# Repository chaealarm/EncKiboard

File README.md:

# EncKiboard V3
RP2040, MX keys with LED, 1 Encoder   

Designed in EasyEDA

## See also
Arduino Board Library(Generic RP2040) : https://github.com/earlephilhower/arduino-pico

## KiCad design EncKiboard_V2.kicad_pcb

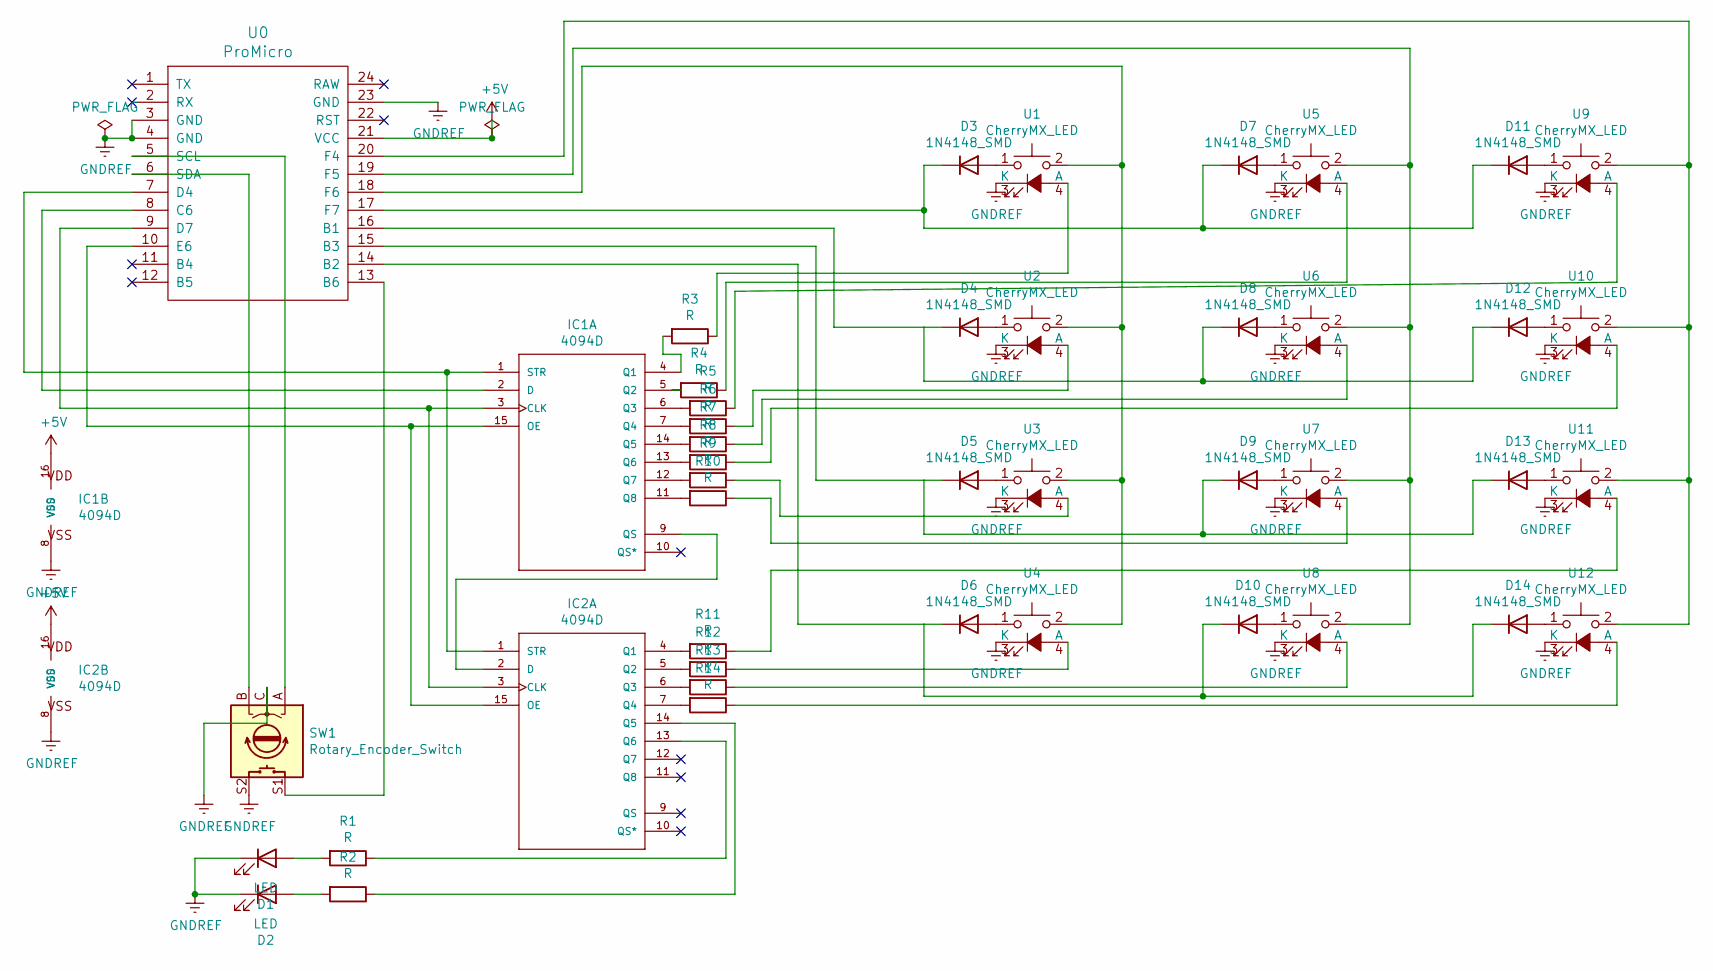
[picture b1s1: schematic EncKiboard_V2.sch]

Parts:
D1, D2: LED; LED_D3.0mm
D3, D4, D5, D6, D7, D8, D9, D10, D11, D12, D13, D14: 1N4148_SMD; D_MELF_Handsoldering
IC1, IC2: 4094D; SO-16_5.3x10.2mm_P1.27mm
R1, R2, R3, R4, R5, R6, R7, R8, R9, R10, R11, R12, R13, R14: R; R_1206_3216Metric_Pad1.30x1.75mm_HandSolder
SW1: Rotary_Encoder_Switch; RotaryEncoder_Alps_EC11E-Switch_Vertical_H20mm
U0: ProMicro
U1, U2, U3, U4, U5, U6, U7, U8, U9, U10, U11, U12: CherryMX_LED; CherryMX_1.00u_PCB_LED

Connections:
+5V: IC1.16 (VDD), IC2.16 (VDD), U0.21 (VCC)
GNDREF: D1.1 (K), D2.1 (K), IC1.8 (VSS), IC2.8 (VSS), SW1.C, SW1.S2, U0.3 (GND), U0.4 (GND), U0.23 (GND), U1.3 (K), U2.3 (K), U3.3 (K), U4.3 (K), U5.3 (K), U6.3 (K), U7.3 (K), U8.3 (K), U9.3 (K), U10.3 (K), U11.3 (K), U12.3 (K)
unnamed: D1.2 (A), R1.2
unnamed: D2.2 (A), R2.2
unnamed: D3.2 (A), U1.1
unnamed: D4.2 (A), U2.1
unnamed: D5.2 (A), U3.1
unnamed: D6.2 (A), U4.1
unnamed: D7.2 (A), U5.1
unnamed: D8.2 (A), U6.1
unnamed: D9.2 (A), U7.1
unnamed: D6.1 (K), D10.1 (K), D14.1 (K), U0.14 (B2)
unnamed: D10.2 (A), U8.1
unnamed: D3.1 (K), D7.1 (K), D11.1 (K), U0.17 (F7)
unnamed: D11.2 (A), U9.1
unnamed: D4.1 (K), D8.1 (K), D12.1 (K), U0.16 (B1)
unnamed: D12.2 (A), U10.1
unnamed: D5.1 (K), D9.1 (K), D13.1 (K), U0.15 (B3)
unnamed: D13.2 (A), U11.1
unnamed: D14.2 (A), U12.1
unnamed: IC1.1 (STR), IC2.1 (STR), U0.7 (D4)
unnamed: IC1.2 (D), U0.8 (C6)
unnamed: IC1.3 (CLK), IC2.3 (CLK), U0.9 (D7)
unnamed: IC1.4 (Q1), R3.2
unnamed: IC1.5 (Q2), R4.2
unnamed: IC1.6 (Q3), R5.2
unnamed: IC1.7 (Q4), R6.2
unnamed: IC1.9 (QS), IC2.2 (D)
unnamed: IC1.11 (Q8), R10.2
unnamed: IC1.12 (Q7), R9.2
unnamed: IC1.13 (Q6), R8.2
unnamed: IC1.14 (Q5), R7.2
unnamed: IC1.15 (OE), IC2.15 (OE), U0.10 (E6)
unnamed: IC2.4 (Q1), R11.2
unnamed: IC2.5 (Q2), R12.2
unnamed: IC2.6 (Q3), R13.2
unnamed: IC2.7 (Q4), R14.2
unnamed: IC2.13 (Q6), R1.1
unnamed: IC2.14 (Q5), R2.1
unnamed: R3.1, U1.4 (A)
unnamed: R4.1, U5.4 (A)
unnamed: R5.1, U9.4 (A)
unnamed: R6.1, U2.4 (A)
unnamed: R7.1, U6.4 (A)
unnamed: R8.1, U10.4 (A)
unnamed: R9.1, U3.4 (A)
unnamed: R10.1, U7.4 (A)
unnamed: R11.1, U11.4 (A)
unnamed: R12.1, U4.4 (A)
unnamed: R13.1, U8.4 (A)
unnamed: R14.1, U12.4 (A)
unnamed: SW1.A, U0.5 (SCL)
unnamed: SW1.B, U0.6 (SDA)
unnamed: SW1.S1, U0.13 (B6)
unnamed: U0.18 (F6), U1.2, U2.2, U3.2, U4.2
unnamed: U0.19 (F5), U5.2, U6.2, U7.2, U8.2
unnamed: U0.20 (F4), U9.2, U10.2, U11.2, U12.2

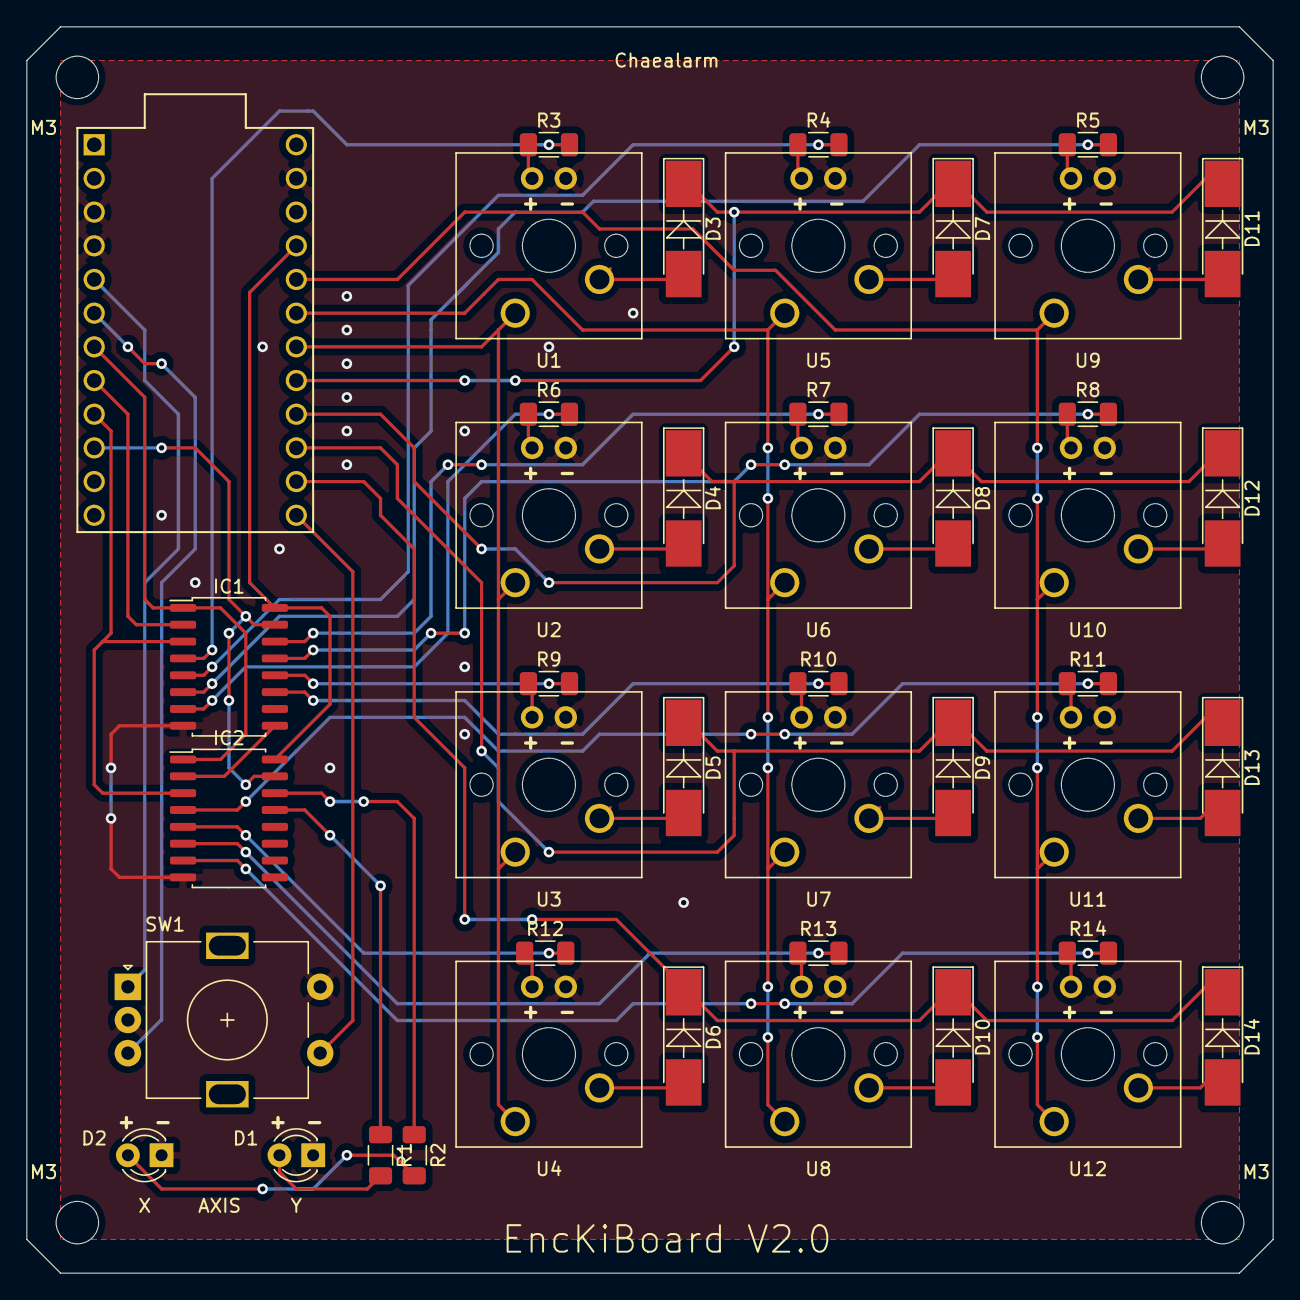
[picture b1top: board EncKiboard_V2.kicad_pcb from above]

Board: 2 copper layers, 94.0 x 94.0 mm, 48 parts (0 on the bottom side), 57 nets.

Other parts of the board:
M3, M3#2, M3#3, M3#4: MountingHole_3.2mm_M3

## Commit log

2021-05-07 Edit diode position
2021-05-07 Edit wrong diode position
2022-10-09 Create LICENSE
2022-10-09 enckiboard v3
2022-10-09 Sample codes
2022-10-14 Add files via upload
    USB Port fix(pats leakage)
    More thicker 5V line
2022-11-13 Add files via upload
    Automatic switch Korean/English when using '/w' or '/r' command
    Some boilerplate add/removed
2022-11-13 Add files via upload
    Automatic switch Korean/English when using '/w' or '/r' command
    Some boilerplate add/removed
    Numeric Keypad(when push encoder)
